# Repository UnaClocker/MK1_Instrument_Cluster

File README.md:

This code cannot be copyrighted, as it was entirely vibe coded via AI, Gemini to be specific. 
The circuit board was based on this design and physically made to fit with STL files which are included. The circuit board is licensed Creative Commons - Attribution.
The STLs were created by me, by hand, in TinkerCAD. They are licensed Create Commons - Attribution.

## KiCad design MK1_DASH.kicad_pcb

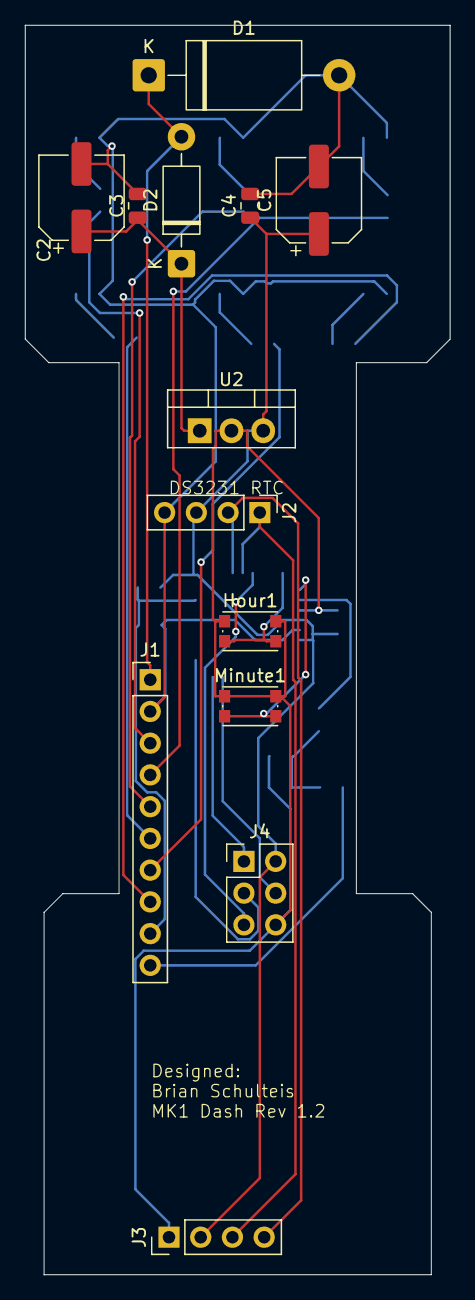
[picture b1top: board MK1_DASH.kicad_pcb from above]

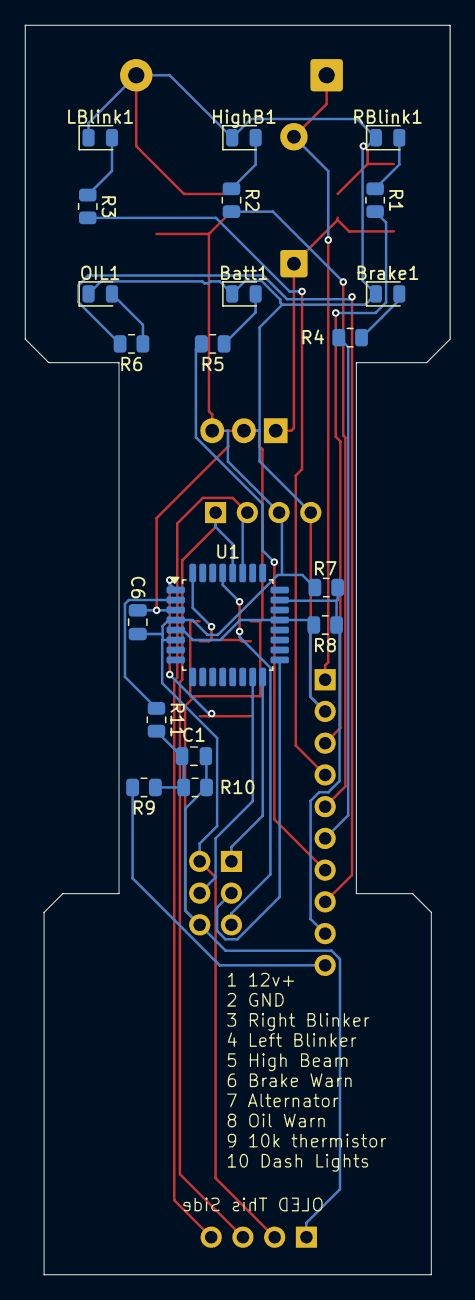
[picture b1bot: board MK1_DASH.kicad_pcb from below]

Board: 2 copper layers, 34.0 x 100.0 mm, 33 parts (20 on the bottom side), 28 nets.

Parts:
Batt1: LED; LED_0805_2012Metric
Brake1: LED; LED_0805_2012Metric
C1, C3, C4, C6: .1uF; C_0805_2012Metric
C2: 50uF 50v; CP_Elec_6.3x4.5
C5: 10uF 16v; CP_Elec_6.3x4.5
D1: SA18A; D_DO-201AE_P15.24mm_Horizontal
D2: 1N4007; D_DO-41_SOD81_P10.16mm_Horizontal
HighB1: LED; LED_0805_2012Metric
Hour1: SW_Push; SW_Push_1P1T_NO_CK_KMR2
J1: Conn_01x10; PinHeader_1x10_P2.54mm_Vertical
J2: RTC; PinHeader_1x04_P2.54mm_Vertical
J3: OLED; PinHeader_1x04_P2.54mm_Vertical
J4: AVR-ISP-6; PinHeader_2x03_P2.54mm_Vertical
LBlink1: LED; LED_0805_2012Metric
Minute1: SW_Push; SW_Push_1P1T_NO_CK_KMR2
OIL1: LED; LED_0805_2012Metric
R1, R2, R3: 4.7K; R_0805_2012Metric
R4, R5, R6: 3.3K; R_0805_2012Metric
R7, R8, R9: 10k; R_0805_2012Metric
R10: 4.7k; R_0805_2012Metric
R11: 1k; R_0805_2012Metric
RBlink1: LED; LED_0805_2012Metric
U1: ATmega328-A; TQFP-32_7x7mm_P0.8mm
U2: LM7805_TO220; TO-220-3_Vertical

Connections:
/Alternator: J1.7, R5.2
/Battery +: D1.1 (A1), D2.2 (A), J1.1
/Brake: J1.6, R4.2
/Dim: R11.1, U1.2 (PD4)
/High Beam: J1.5, R2.2
/Hour: Hour1.2, U1.32 (PD2)
/L Blinker: J1.4, R3.2
/MISO: J4.1 (MISO), U1.16 (PB4)
/MOSI: J4.4 (MOSI), U1.15 (PB3)
/Minute: Minute1.2, U1.1 (PD3)
/Oil: J1.8, R6.2
/Parking Lights: J1.10, R9.2
/R Blinker: J1.3, R1.2
/RST: J4.5 (~RST), U1.29 (~RESET/PC6)
/SCK: J4.3 (SCK), U1.17 (PB5)
/SCL: J2.1, J3.3, U1.28 (PC5)
/SDA: J2.2, J3.4, U1.27 (PC4)
/Temp: J1.9, R7.1, R8.1, U1.23 (PC0)
GND: Batt1.1 (K), Brake1.1 (K), C1.2, C2.2, C3.2, C4.2, C5.2, C6.2, D1.2 (A2), HighB1.1 (K), Hour1.1, J1.2, J2.4, J3.1, J4.6 (GND), LBlink1.1 (K), Minute1.1, OIL1.1 (K), R8.2, R10.2, RBlink1.1 (K), U1.3 (GND), U1.5 (GND), U1.21 (GND), U2.2 (GND)
unnamed: Batt1.2 (A), R5.1
unnamed: Brake1.2 (A), R4.1
unnamed: C1.1, R9.1, R10.1, R11.2
unnamed: C2.1, C3.1, D2.1 (K), U2.1 (VI)
unnamed: HighB1.2 (A), R2.1
unnamed: LBlink1.2 (A), R3.1
unnamed: OIL1.2 (A), R6.1
unnamed: R1.1, RBlink1.2 (A)
VCC: C4.1, C5.1, C6.1, J2.3, J3.2, J4.2 (VCC), R7.2, U1.4 (VCC), U1.6 (VCC), U2.3 (VO)
